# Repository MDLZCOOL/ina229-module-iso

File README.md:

# 电压电流模块（全隔离版）

## 简介

采用ina229前端+cs32l010f8u6单片机做的信号供电全隔离的电压电流模组，采用串口MODBUS输出，支持0-85V电压测量。

至于为什么是cs32l010f8u6，最近偶然得到几百片这个mcu，想办法用掉吧~

## 使用须知

- 支持测量的电压范围是0-85V
- 支持测量的最大电流与采样电阻有关，计算公式为`I_MAX ≤ 0.16384 / R_SHUNT`，其中R_SHUNT单位为欧姆，I单位安培
- 用户需要同时接入3.3V和5V电平，其中丝印3.3V的位置可以接入其他电平，作为串口RXTX的输出电平，5V位置只能接入5V
- “全隔离”指信号与供电全隔离，如果用户供电或信号的地与被测电流电压信号的地导通，则不隔离，但是仍可正常使用

## 上位机

- 上位机可以用于更改模块MODBUS地址、采样电阻信息、最大预期电流、校准系数
- 需要注意的是，最大预期电流公式见“使用须知”，并不是无限大的
- 所以用户更改采样电阻以适配不同精度，不同量程后，需要手动更新采样电阻信息，也可能需要重新设置校准系数
- 校准系数 = 实测值 ÷ 上位机显示值
- 上位机可以直接进行固件升级，连接好后，点击“升级”，选择新的bin文件即可进行升级，升级不会导致配置信息丢失。如果升级失败，可以“按住按键”并重新上电后重试

## Modbus 寄存器表

### 通信参数

| 项目                   | 值                                                           |
| ---------------------- | ------------------------------------------------------------ |
| 物理接口               | 串口（UART，隔离输出）                                       |
| 协议                   | Modbus RTU                                                   |
| 波特率                 | 115200 bps                                                   |
| 数据位 / 校验 / 停止位 | 8 / None / 1                                                 |
| 从机地址               | 可配置，默认 1                                               |
| 实现的功能码           | `0x03` 读保持寄存器、`0x06` 写单个寄存器、`0x10` 写多个寄存器 |

### 数据格式说明

- 浮点数（float）：IEEE-754 单精度，占用 2 个连续寄存器高位字在前（Big-Endian）。即地址 N 存高 16 位、地址 N+1 存低 16 位，每个寄存器内部字节大端。
- 整型（uint16）：占用 1 个寄存器，大端。
- 测量数据区为只读（RO），用于获取测量数据。
- 配置参数区为可读写（RW）：修改后先存于 RAM，需向 `0x0110` 写入保存指令才会写入 Flash。

### 保持寄存器 — 测量数据（只读）

| 地址(hex) | 地址(dec) | 寄存器范围    | 名称                 | 类型(寄存器数) | 单位 | 说明                            |
| --------- | --------- | ------------- | -------------------- | -------------- | ---- | ------------------------------- |
| 0x0000    | 0         | 0x0000–0x0001 | Voltage（电压）      | float (2)      | V    | 总线电压                        |
| 0x0002    | 2         | 0x0002–0x0003 | Current（电流）      | float (2)      | A    | 电流                            |
| 0x0004    | 4         | 0x0004–0x0005 | Power（功率）        | float (2)      | W    | 功率                            |
| 0x0006    | 6         | 0x0006–0x0007 | Charge（电荷量）     | float (2)      | C    | 累计电荷量                      |
| 0x0008    | 8         | 0x0008–0x0009 | Temperature（温度）  | float (2)      | °C   | 内部温度                        |
| 0x000A    | 10        | 0x000A–0x000B | Energy（能量）       | float (2)      | J    | 累计能量，1 Wh = 3600 J         |
| 0x000C    | 12        | 0x000C        | Error Code（错误码） | uint16 (1)     | —    | INA229 诊断/告警位域，见第 5 节 |

### 保持寄存器 — 配置参数（可读写）

| 地址(hex) | 地址(dec) | 寄存器范围    | 名称       | 类型(寄存器数) | 单位   | 默认值 | 说明                                                   |
| --------- | --------- | ------------- | ---------- | -------------- | ------ | ------ | ------------------------------------------------------ |
| 0x0100    | 256       | 0x0100        | ModbusAddr | uint16 (1)     | —      | 1      | 本机 Modbus 从机地址                                   |
| 0x0101    | 257       | 0x0101–0x0102 | RshuntOhm  | float (2)      | Ω      | 0.01   | 采样电阻值 R_SHUNT；修改后需用 0x0103 配合标定为新量程 |
| 0x0103    | 259       | 0x0103–0x0104 | IexpMax    | float (2)      | A      | 15.0   | 最大预期电流 I_MAX；约束：`I_MAX ≤ 0.16384 / R_SHUNT`  |
| 0x0105    | 261       | 0x0105        | ShuntOVTｈ | uint16 (1)     | —      | 0x7FFF | 分流过压阈值（SOVL）                                   |
| 0x0106    | 262       | 0x0106        | ShuntUVTh  | uint16 (1)     | —      | 0x8000 | 分流欠压阈值（SUVL）                                   |
| 0x0107    | 263       | 0x0107        | BusOVTｈ   | uint16 (1)     | —      | 0x7FFF | 总线过压阈值（BOVL）                                   |
| 0x0108    | 264       | 0x0108        | BusUVTh    | uint16 (1)     | —      | 0x8000 | 总线欠压阈值（BUVL）                                   |
| 0x0109    | 265       | 0x0109        | TempOLTh   | uint16 (1)     | —      | 0x7FFF | 温度超限阈值（TEMP_LIMIT）                             |
| 0x010A    | 266       | 0x010A        | PowerOLTh  | uint16 (1)     | —      | 0x7FFF | 功率超限阈值（PWR_LIMIT）                              |
| 0x010B    | 267       | 0x010B–0x010C | VoltageK   | float (2)      | —      | 1.0    | 电压校准系数 = `实测值 ÷ 显示值`                       |
| 0x010D    | 269       | 0x010D–0x010E | CurrentK   | float (2)      | —      | 1.0    | 电流校准系数 = `实测值 ÷ 显示值`                       |
| 0x010F    | 271       | 0x010F        | RshuntPPM  | uint16 (1)     | ppm/°C | 50     | 采样电阻温度系数                                       |
| 0x0110    | 272       | 0x0110        | SaveCmd    | uint16 (1)     | —      | 0      | 写命令：写入 `0x4B56` 将当前配置保存到 Flash           |
| 0x0111    | 273       | 0x0111        | BootCmd    | uint16 (1)     | —      | 0      | 写命令：写入 `0x4B4F` 重启进入固件升级模式             |

### 错误码（Error Code，0x000C）位定义

| Bit  | 宏 / 名称 | 含义           |
| ---- | --------- | -------------- |
| 0    | MEMSTAT   | 存储器校验错误 |
| 1    | CNVRF     | 转换完成标志   |
| 2    | POL       | 功率超限       |
| 3    | BUSUL     | 总线欠压       |
| 4    | BUSOL     | 总线过压       |
| 5    | SHNTUL    | 分流欠压       |
| 6    | SHNTOL    | 分流过压       |
| 7    | TMPOL     | 温度超限       |
| 8    | OFFLINE   | 芯片离线       |
| 9    | MATHOF    | 数学计算溢出   |
| 10   | CHARGEOF  | 电荷寄存器溢出 |
| 11   | ENERGYOF  | 能量寄存器溢出 |

### 使用要点

- 读实时数据：用功能码 `0x03` 读取 0x0000–0x000C。
- 改配置并保存：先写 0x0100–0x010F 中目标寄存器，再向 0x0110 写 `0x4B56` 保存。
- 固件升级：向 0x0111 写 `0x4B4F` 进入升级模式，再用 YMODEM 方式烧录新 bin。
- 校准：`校准系数 = 实测值 ÷ 上位机显示值`，写入电压电流校准系数后保存。
- 量程约束：更换采样电阻后需重设采样电阻信息与最大预期电流，并满足 `I_MAX ≤ 0.16384 / R_SHUNT`，必要时重新校准系数。

## 目录结构

- [./Hardware](Hardware)下为硬件设计，使用Kicad 8.0以上版本打开
- [./Firmware](Firmware)下为编译好的固件
- [./Software](Software)下为mcu源码
- [./Upper](Upper)下为上位机源码
- [./Document](Document)下为mcu的ds和pack

## Changelog

20260713更新：初始化仓库。硬件完成，软件还没写，已送去jlc打样pcb+smt。。希望这个究极灵车mcu不要翻车了

20260801更新：V1.0，完成上位机，上位机实现了数据测量、参数修改、固件更新。完成下位机Application+Bootloader，实现modbus通信，传感器读取，参数保存，固件更新。

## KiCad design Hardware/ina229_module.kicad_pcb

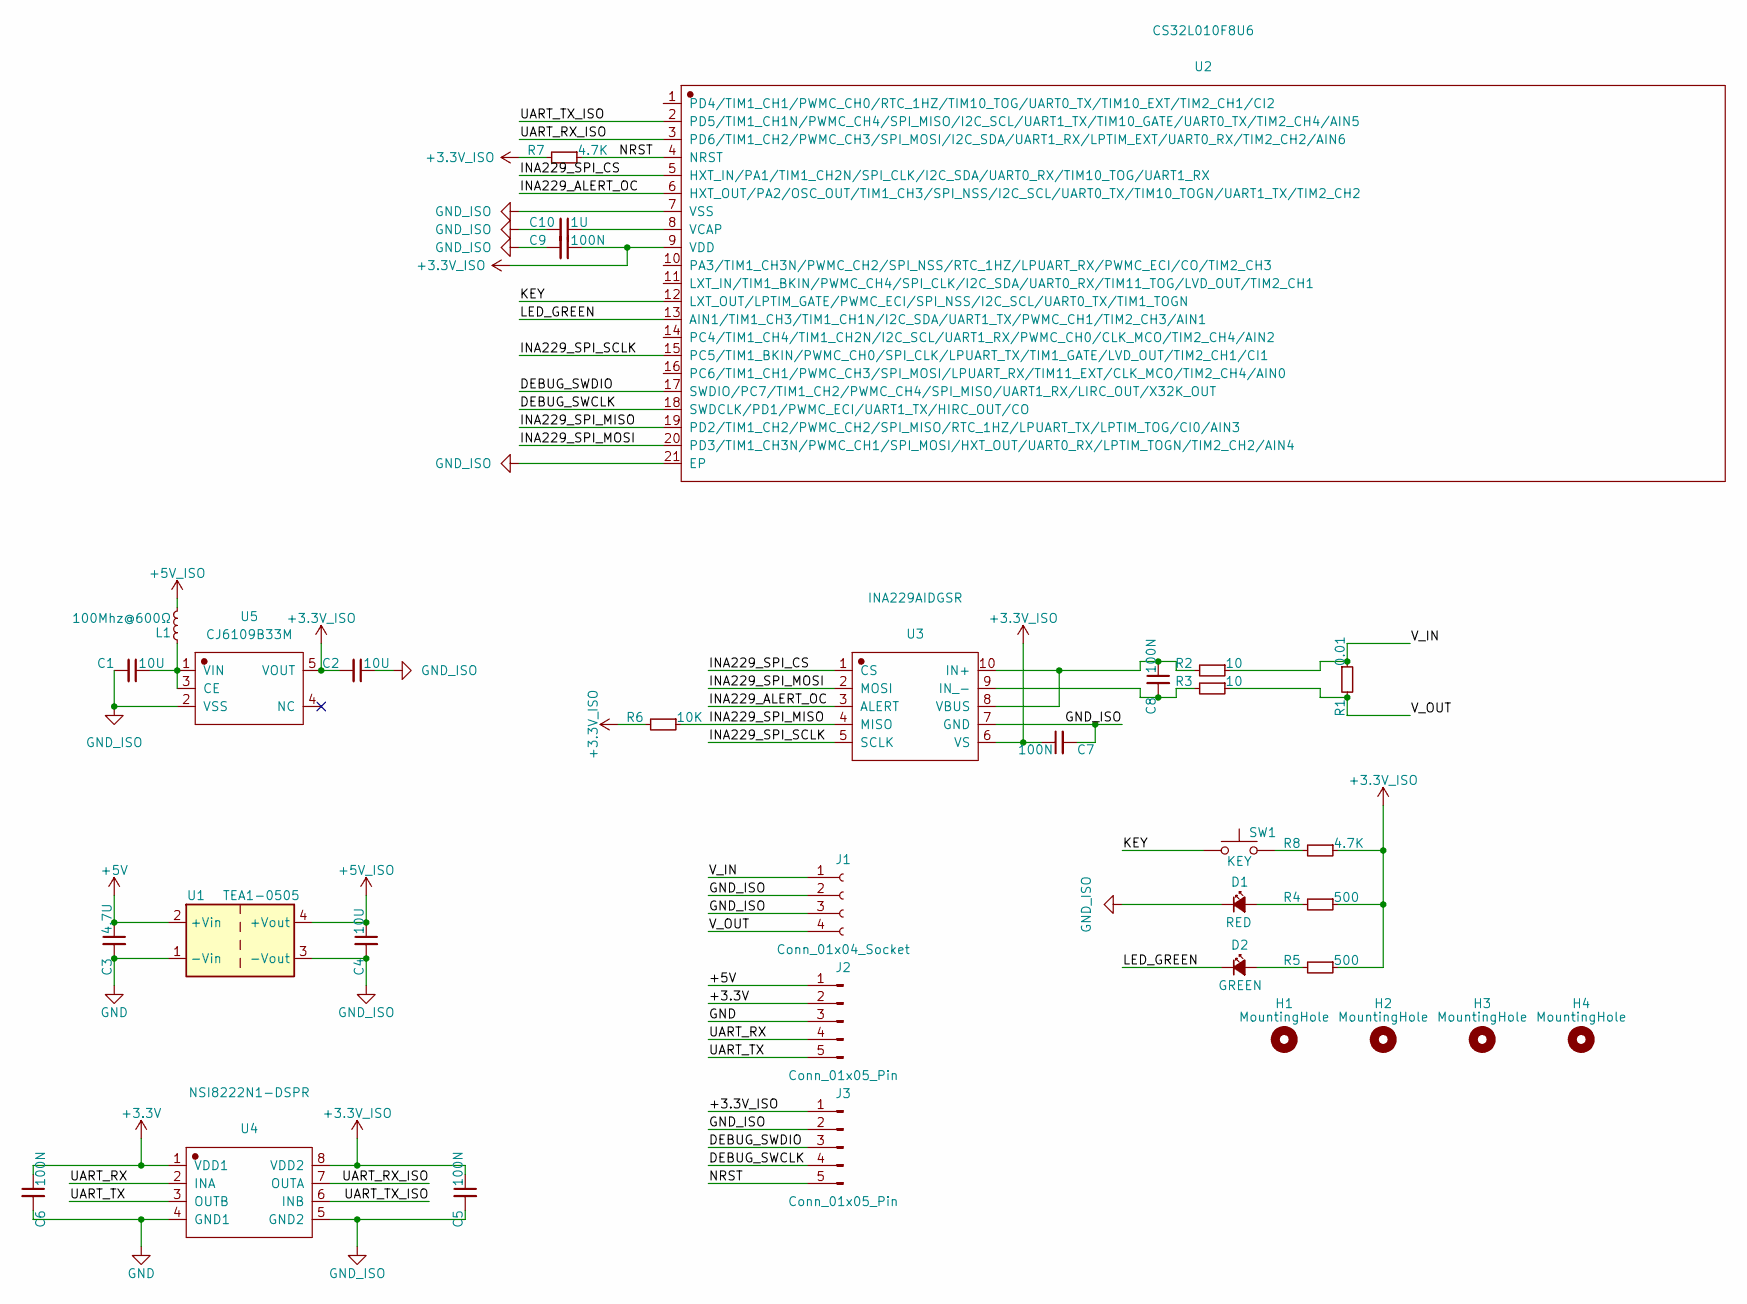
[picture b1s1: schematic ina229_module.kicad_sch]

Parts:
C1, C2, C4: 10U; C_0603_1608Metric_Pad1.08x0.95mm_HandSolder
C3: 4.7U; C_0603_1608Metric_Pad1.08x0.95mm_HandSolder
C5, C6, C7, C8, C9: 100N; C_0603_1608Metric_Pad1.08x0.95mm_HandSolder
C10: 1U; C_0603_1608Metric_Pad1.08x0.95mm_HandSolder
D1: RED; LED_0603_1608Metric_Pad1.05x0.95mm_HandSolder
D2: GREEN; LED_0603_1608Metric_Pad1.05x0.95mm_HandSolder
H1, H2, H3, H4: MountingHole; MountingHole_3.2mm_M3_ISO7380
J1: Conn_01x04_Socket; TerminalBlock_Phoenix_MKDS-1,5-4-5.08_1x04_P5.08mm_Horizont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
J2: Conn_01x05_Pin; JST_XH_B5B-XH-A_1x05_P2.50mm_Vertical
J3: Conn_01x05_Pin; PinHeader_1x05_P2.54mm_Vertical
L1: 100Mhz@600Ω; L_0603_1608Metric_Pad1.05x0.95mm_HandSolder
R1: 0.01; R_2512_6332Metric_Pad1.40x3.35mm_HandSolder
R2, R3: 10; R_0603_1608Metric_Pad0.98x0.95mm_HandSolder
R4, R5: 500; R_0603_1608Metric_Pad0.98x0.95mm_HandSolder
R6: 10K; R_0603_1608Metric_Pad0.98x0.95mm_HandSolder
R7, R8: 4.7K; R_0603_1608Metric_Pad0.98x0.95mm_HandSolder
SW1: KEY; SW_SPST_B3U-1000P
U1: TEA1-0505; Converter_DCDC_TRACO_TEA1-xxxx_THT
U2: CS32L010F8U6; WFQFN-20_L3.0-W3.0-P0.40-TL-EP1.7
U3: INA229AIDGSR; VSSOP-10_L3.0-W3.0-P0.50-LS4.9-BL
U4: NSI8222N1-DSPR; SOP-8_L4.9-W3.9-P1.27-LS6.0-BL
U5: CJ6109B33M; SOT-23-5_L2.9-W1.6-P0.95-LS2.8-BR

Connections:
+3.3V: C6.1, J2.2, U4.1 (VDD1)
+3.3V_ISO: C2.2, C5.1, C7.1, C9.1, J3.1, R4.1, R5.1, R6.2, R7.2, R8.1, U2.9 (VDD), U3.6 (VS), U4.8 (VDD2), U5.5 (VOUT)
+5V: C3.1, J2.1, U1.2 (+Vin)
+5V_ISO: C4.1, L1.2, U1.4 (+Vout)
/DEBUG_SWCLK: J3.4, U2.18 (SWDCLK/PD1/PWMC_ECI/UART1_TX/HIRC_OUT/CO)
/DEBUG_SWDIO: J3.3, U2.17 (SWDIO/PC7/TIM1_CH2/PWMC_CH4/SPI_MISO/UA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)
/INA229_ALERT_OC: U2.6 (HXT_OUT/PA2/OSC_OUT/TIM1_CH3/SPI_NSS/I2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), U3.3 (ALERT)
/INA229_SPI_CS: U2.5 (HXT_IN/PA1/TIM1_CH2N/SPI_CLK/I2C_SDA/UA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), U3.1 (CS)
/INA229_SPI_MISO: R6.1, U2.19 (PD2/TIM1_CH2/PWMC_CH2/SPI_MISO/RTC_1HZ/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), U3.4 (MISO)
/INA229_SPI_MOSI: U2.20 (PD3/TIM1_CH3N/PWMC_CH1/SPI_MOSI/HXT_OUT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), U3.2 (MOSI)
/INA229_SPI_SCLK: U2.15 (PC5/TIM1_BKIN/PWMC_CH0/SPI_CLK/LPUART_T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), U3.5 (SCLK)
/KEY: SW1.1, U2.12 (LXT_OUT/LPTIM_GATE/PWMC_ECI/SPI_NSS/I2C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)
/LED_GREEN: D2.1 (K), U2.13 (AIN1/TIM1_CH3/TIM1_CH1N/I2C_SDA/UART1_T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)
/NRST: J3.5, R7.1, U2.4 (NRST)
/UART_RX: J2.4, U4.2 (INA)
/UART_RX_ISO: U2.3 (PD6/TIM1_CH2/PWMC_CH3/SPI_MOSI/I2C_SDA/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), U4.7 (OUTA)
/UART_TX: J2.5, U4.3 (OUTB)
/UART_TX_ISO: U2.2 (PD5/TIM1_CH1N/PWMC_CH4/SPI_MISO/I2C_SCL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), U4.6 (INB)
/V_IN: J1.1, R1.1, R2.1
/V_OUT: J1.4, R1.2, R3.1
GND: C3.2, C6.2, J2.3, U1.1 (-Vin), U4.4 (GND1)
GND_ISO: C1.2, C2.1, C4.2, C5.2, C7.2, C9.2, C10.2, D1.1 (K), J1.2, J1.3, J3.2, U1.3 (-Vout), U2.7 (VSS), U2.21 (EP), U3.7 (GND), U4.5 (GND2), U5.2 (VSS)
unnamed: D1.2 (A), R4.2
unnamed: D2.2 (A), R5.2
unnamed: R8.2, SW1.2
unnamed: C10.1, U2.8 (VCAP)
unnamed: C8.1, R2.2, U3.8 (VBUS), U3.10 (IN+)
unnamed: C8.2, R3.2, U3.9 (IN_-)
unnamed: C1.1, L1.1, U5.1 (VIN), U5.3 (CE)

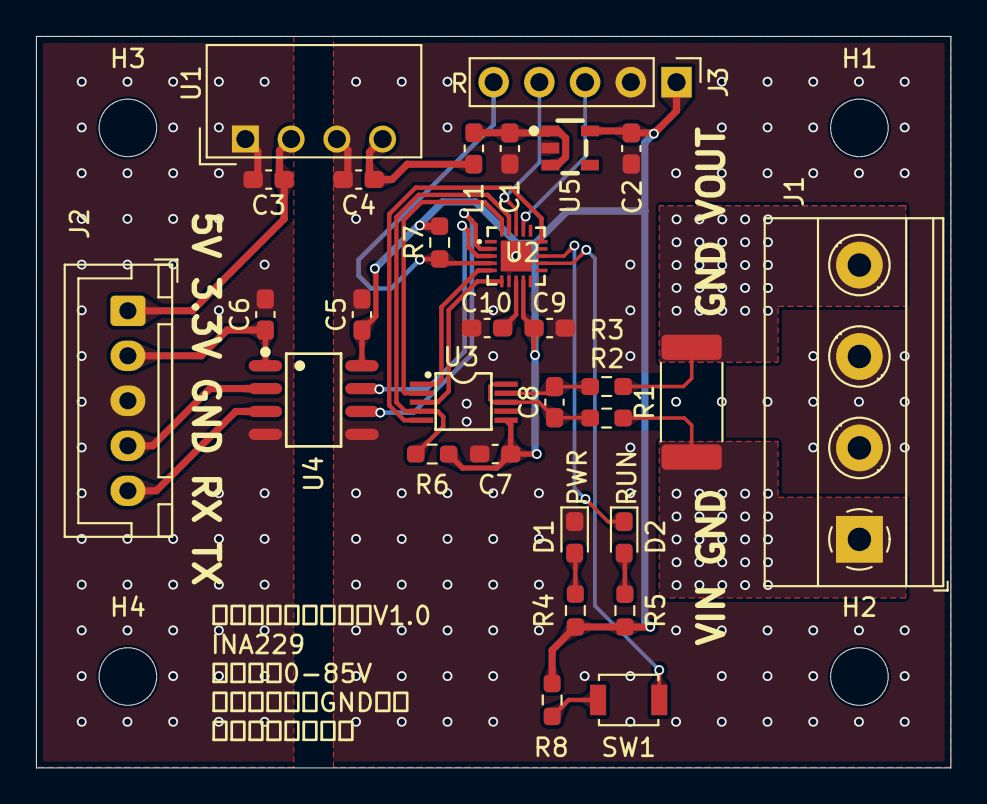
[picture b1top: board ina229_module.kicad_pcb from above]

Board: 2 copper layers, 50.8 x 40.6 mm, 34 parts (0 on the bottom side), 29 nets.

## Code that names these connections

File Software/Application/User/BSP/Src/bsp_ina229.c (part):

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/*
    È«¸ôÀëµçÑ¹µçÁ÷Ä£¿éV1.0

    PC5  --->  INA229_SPI_SCK
    PD3  --->  INA229_SPI_MOSI
    PD2  --->  INA229_SPI_MISO
    PA1  --->  INA229_SPI_CS
    PA2  --->  INA229_ALERT
*/

#define ALL_INA229_GPIO_CLK_ENABLE() \
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

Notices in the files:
Software/Application/User/BSP/Src/bsp_ina229.c:
SPDX-FileCopyrightText: 2026 MDLZCOOL <mdlzcool@foxmail.com>
SPDX-License-Identifier: Apache-2.0
